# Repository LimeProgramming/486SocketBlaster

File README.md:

# Ignore this for the moment please need to fix it when I have the drive to. Sorry but thanks for looking. 

# 486SocketBlaster

486SocketBlaster is a simple voltage adapter for 486 processors. It allows you
to use a 3-volt 486 CPU on an older 5-volt-only motherboard. For example you
can use a DX4 or an Am5x86 on an old 486 motherboard that would normally only
work with 5-volt CPUs. This basically converts any 3-volt CPU to an "Overdrive".

# How does it work ?

It is really simple: All CPU pins are passed through to the motherboard socket,
except for the Vcc. Those are connected to the output of a mini buck converter
that can be soldered to the 486SocketBlaster board.

# Soldering/Assembly Instructions

This board is not the easiest thing to solder, but can be done with a standard
soldering iron and some patience.
The best way to solder the headers is to start with the innermost one and work
outwards in a spiral manner alternating between the top and bottom side as
needed (see image below). This way you only work on the outside and can easily
reach all the pins.

A desoldering gun may be useful when you accidentally clog up other holes. But
it is probably best to be very careful and avoid clogging them in the first
place. Also using flux makes it easier.

Please make sure you check the solder joints (also check for continuity) before
you add another row of headers on the same side, because the new row will
permanently block your access to the solder joints!
Desoldering a header is almost impossible even with a desoldering gun due to the
very tight hole tolerances.
So it has to be soldered correctly from the first try.

# Voltage regulator

The 486SocketBlaster can be powered by a cheap of-the-shelf buck converter, or
by an external one. The circuit board accepts two common types of small voltage
buck converters, usually found using keywords like "mini buck converter".
These are commonly rated at up to 3A of current. Given that 3-volt 486 CPUs are
usually very efficient (the DX4-100 is rated at max 3.55/5.22W typical/max) such
a regulator should be adequate in most cases.

If you are planning to overclock or to use a more power hungry CPU, please use
an external regulation circuit.

# WARNING!!!

Please make sure you know what you are doing!
Improper assembly/settings/use can damage both your precious motherboard and your precious CPU!

# Bonus Features

- External Power Header. This can be used either for monitoring the CPU voltage,
or for providing power externally, either with an external power supply or an
external voltage regulator.
- CPUMUL Header for selecting/overriding the CPU multiplier. This may be useful
for reducing the multiplier of a DX4 to 2x (66MHz) or Am5x86 to 3x (100MHz).

# Bill of materials

Item                            | ##  | Description
--------------------------------|-----|--------------------------------------------------------
mini buck converter             | 1   | We support two common sizes: 22x17mm and 18x12mm. These usually have chips like MP1584, MP2307 and others
40pin SIP pin header (male)     | 5   | Single-row round pin 2.54mm pitch (male). Socket pin diameter: 0.5mm, PCB pin diameter: 0.6mm. (see photo below)
40pin SIP socket header (female)| 5   | Single-row round pin sockets, 2.54mm pitch. PCB pin diameter: 0.5mm. (see photo below) 
SMD Capacitors                  | 4   | 10uF SMD 1206
Through-hole Capacitor          | 1   | 10uF ceramic through-hole capacitor
3-pin header 2.54mm pitch       | 1   | Header used for selecting the CPU Multiplier (CPUMUL)
Jumper 2.54mm pitch             | 1   | A jumper to for the CPUMUL header

Please note that the headers are a very tight fit. So please make sure that you get headers of the correct pin diameter.

With the limited testing I have done so far, it seems that you need at least
one 10uF through-hole ceramic capacitor, otherwise the voltage ripple is too
high and the system can become unstable with a DX4 @ 100MHz, using a cheap
MP1584-based buck converter.

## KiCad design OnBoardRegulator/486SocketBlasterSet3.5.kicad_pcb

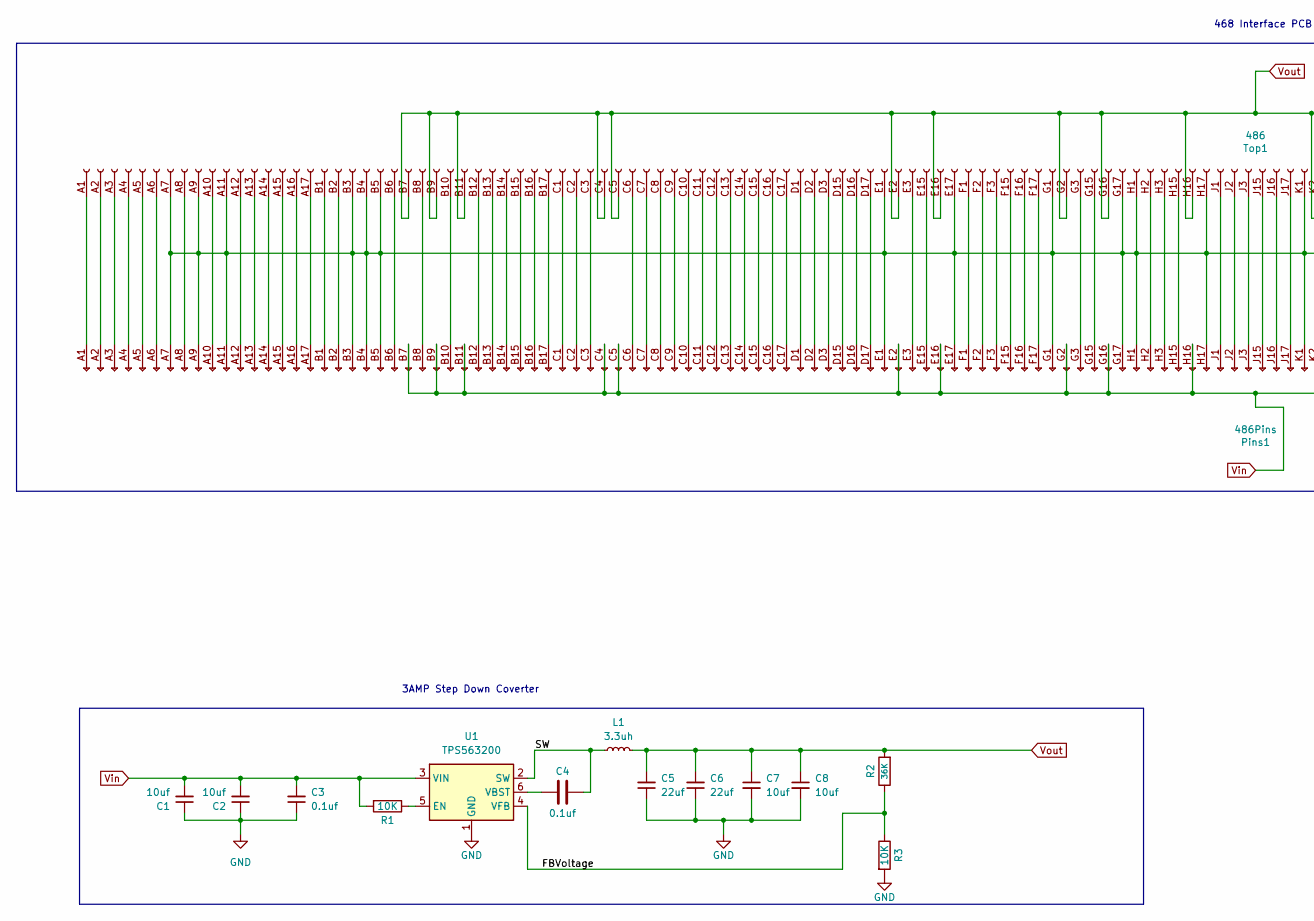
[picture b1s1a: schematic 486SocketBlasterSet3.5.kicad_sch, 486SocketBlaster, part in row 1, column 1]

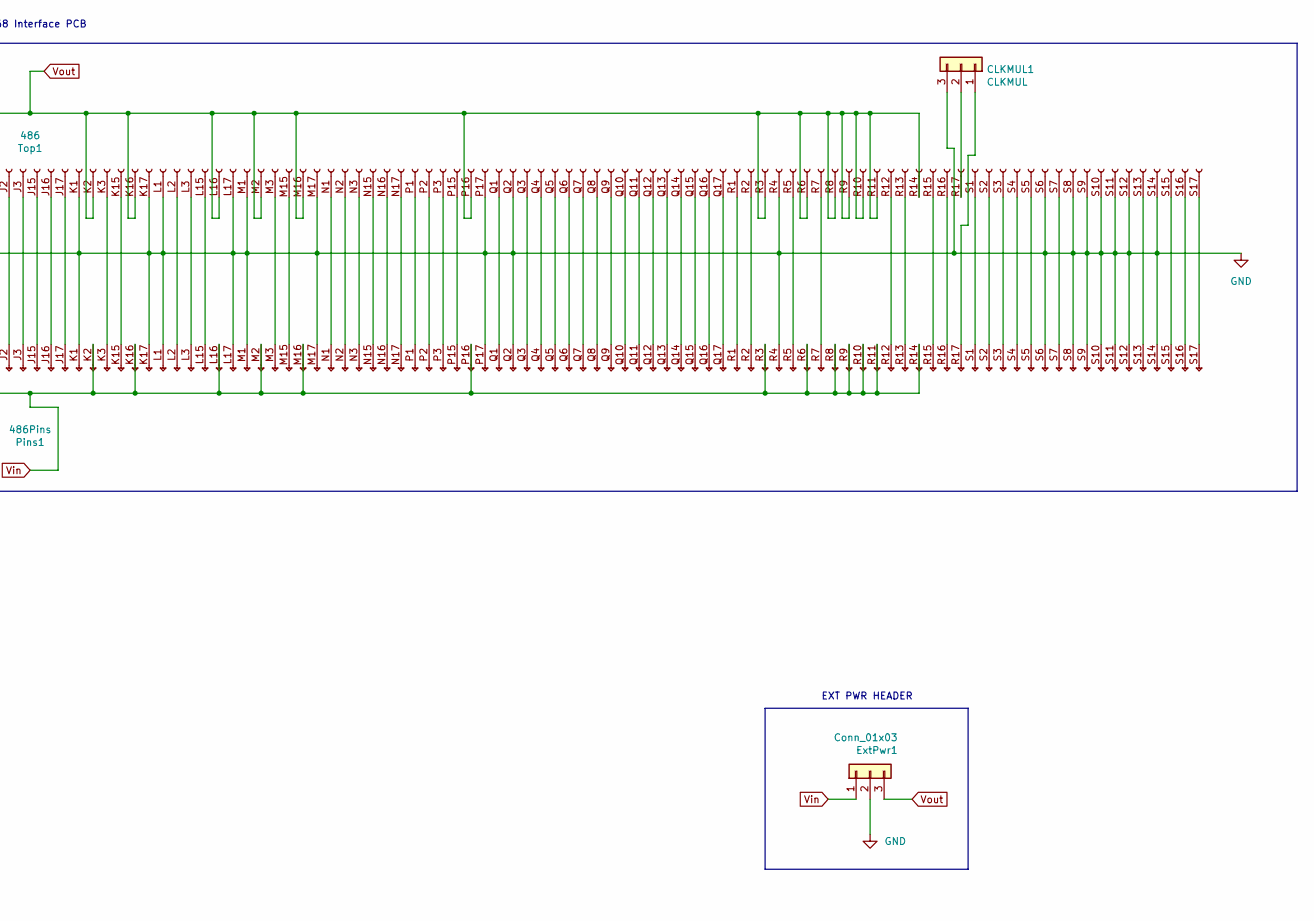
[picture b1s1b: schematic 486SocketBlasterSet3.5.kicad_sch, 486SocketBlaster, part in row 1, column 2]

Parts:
C1, C2, C7, C8: 10uf; C_0805_2012Metric; JLCPCB C15850
C3, C4: 0.1uf; C_0805_2012Metric; JLCPCB C49678
C5, C6: 22uf; C_1206_3216Metric; JLCPCB C12891
CLKMUL1: CLKMUL; PinHeader_1x03_P2.54mm_Vertical
ExtPwr1: Conn_01x03; PinHeader_1x03_P2.54mm_Vertical
L1: 3.3uh; L_5.5x5.5; JLCPCB C436534
Pins1: 486Pins; 486_168pga_pins
R1, R3: 10K; R_0603_1608Metric; JLCPCB C25804
R2: 36K; R_0603_1608Metric; JLCPCB for set C23147
Top1: 486; 486_168pga_socket
U1: TPS563200; SOT-23-6; LCSC C97253

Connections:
/FBVoltage: R2.1, R3.1, U1.4 (VFB)
/SW: C4.2, L1.1, U1.2 (SW)
GND: C1.1, C2.1, C3.1, C5.1, C6.1, C7.2, C8.2, CLKMUL1.3, ExtPwr1.2, Pins1.A7 (Pin_7), Pins1.A9 (Pin_9), Pins1.A11 (Pin_11), Pins1.B3 (Pin_3), Pins1.B4 (Pin_4), Pins1.B5 (Pin_5), Pins1.E1 (Pin_1), Pins1.E17 (Pin_17), Pins1.G1 (Pin_1), Pins1.G17 (Pin_17), Pins1.H1 (Pin_1), Pins1.H17 (Pin_17), Pins1.K1 (Pin_1), Pins1.K17 (Pin_17), Pins1.L1 (Pin_1), Pins1.L17 (Pin_17), Pins1.M1 (Pin_1), Pins1.M17 (Pin_17), Pins1.P17 (Pin_17), Pins1.Q2 (Pin_2), Pins1.R4 (Pin_4), Pins1.S6 (Pin_6), Pins1.S8 (Pin_8), Pins1.S9 (Pin_9), Pins1.S10 (Pin_10), Pins1.S11 (Pin_11), Pins1.S12 (Pin_12), Pins1.S14 (Pin_14), R3.2, Top1.A7 (Pin_7), Top1.A9 (Pin_9), Top1.A11 (Pin_11), Top1.B3 (Pin_3), Top1.B4 (Pin_4), Top1.B5 (Pin_5), Top1.E1 (Pin_1), Top1.E17 (Pin_17), Top1.G1 (Pin_1), Top1.G17 (Pin_17), Top1.H1 (Pin_1), Top1.H17 (Pin_17), Top1.K1 (Pin_1), Top1.K17 (Pin_17), Top1.L1 (Pin_1), Top1.L17 (Pin_17), Top1.M1 (Pin_1), Top1.M17 (Pin_17), Top1.P17 (Pin_17), Top1.Q2 (Pin_2), Top1.R4 (Pin_4), Top1.S6 (Pin_6), Top1.S8 (Pin_8), Top1.S9 (Pin_9), Top1.S10 (Pin_10), Top1.S11 (Pin_11), Top1.S12 (Pin_12), Top1.S14 (Pin_14), U1.1 (GND)
unnamed: C4.1, U1.6 (VBST)
unnamed: CLKMUL1.1, Pins1.R17 (Pin_17)
unnamed: CLKMUL1.2, Top1.R17 (Pin_17)
unnamed: Pins1.A1 (Pin_1), Top1.A1 (Pin_1)
unnamed: Pins1.A2 (Pin_2), Top1.A2 (Pin_2)
unnamed: Pins1.A3 (Pin_3), Top1.A3 (Pin_3)
unnamed: Pins1.A4 (Pin_4), Top1.A4 (Pin_4)
unnamed: Pins1.A5 (Pin_5), Top1.A5 (Pin_5)
unnamed: Pins1.A6 (Pin_6), Top1.A6 (Pin_6)
unnamed: Pins1.A8 (Pin_8), Top1.A8 (Pin_8)
unnamed: Pins1.A10 (Pin_10), Top1.A10 (Pin_10)
unnamed: Pins1.A12 (Pin_12), Top1.A12 (Pin_12)
unnamed: Pins1.A13 (Pin_13), Top1.A13 (Pin_13)
unnamed: Pins1.A14 (Pin_14), Top1.A14 (Pin_14)
unnamed: Pins1.A15 (Pin_15), Top1.A15 (Pin_15)
unnamed: Pins1.A16 (Pin_16), Top1.A16 (Pin_16)
unnamed: Pins1.A17 (Pin_17), Top1.A17 (Pin_17)
unnamed: Pins1.B1 (Pin_1), Top1.B1 (Pin_1)
unnamed: Pins1.B2 (Pin_2), Top1.B2 (Pin_2)
unnamed: Pins1.B6 (Pin_6), Top1.B6 (Pin_6)
unnamed: Pins1.B8 (Pin_8), Top1.B8 (Pin_8)
unnamed: Pins1.B10 (Pin_10), Top1.B10 (Pin_10)
unnamed: Pins1.B12 (Pin_12), Top1.B12 (Pin_12)
unnamed: Pins1.B13 (Pin_13), Top1.B13 (Pin_13)
unnamed: Pins1.B14 (Pin_14), Top1.B14 (Pin_14)
unnamed: Pins1.B15 (Pin_15), Top1.B15 (Pin_15)
unnamed: Pins1.B16 (Pin_16), Top1.B16 (Pin_16)
unnamed: Pins1.B17 (Pin_17), Top1.B17 (Pin_17)
unnamed: Pins1.C1 (Pin_1), Top1.C1 (Pin_1)
unnamed: Pins1.C2 (Pin_2), Top1.C2 (Pin_2)
unnamed: Pins1.C3 (Pin_3), Top1.C3 (Pin_3)
unnamed: Pins1.C6 (Pin_6), Top1.C6 (Pin_6)
unnamed: Pins1.C7 (Pin_7), Top1.C7 (Pin_7)
unnamed: Pins1.C8 (Pin_8), Top1.C8 (Pin_8)
unnamed: Pins1.C9 (Pin_9), Top1.C9 (Pin_9)
unnamed: Pins1.C10 (Pin_10), Top1.C10 (Pin_10)
unnamed: Pins1.C11 (Pin_11), Top1.C11 (Pin_11)
unnamed: Pins1.C12 (Pin_12), Top1.C12 (Pin_12)
unnamed: Pins1.C13 (Pin_13), Top1.C13 (Pin_13)
unnamed: Pins1.C14 (Pin_14), Top1.C14 (Pin_14)
unnamed: Pins1.C15 (Pin_15), Top1.C15 (Pin_15)
unnamed: Pins1.C16 (Pin_16), Top1.C16 (Pin_16)
unnamed: Pins1.C17 (Pin_17), Top1.C17 (Pin_17)
unnamed: Pins1.D1 (Pin_1), Top1.D1 (Pin_1)
unnamed: Pins1.D2 (Pin_2), Top1.D2 (Pin_2)
unnamed: Pins1.D3 (Pin_3), Top1.D3 (Pin_3)
unnamed: Pins1.D15 (Pin_15), Top1.D15 (Pin_15)
unnamed: Pins1.D16 (Pin_16), Top1.D16 (Pin_16)
unnamed: Pins1.D17 (Pin_17), Top1.D17 (Pin_17)
unnamed: Pins1.E3 (Pin_3), Top1.E3 (Pin_3)
unnamed: Pins1.E15 (Pin_15), Top1.E15 (Pin_15)
unnamed: Pins1.F1 (Pin_1), Top1.F1 (Pin_1)
unnamed: Pins1.F2 (Pin_2), Top1.F2 (Pin_2)
unnamed: Pins1.F3 (Pin_3), Top1.F3 (Pin_3)
unnamed: Pins1.F15 (Pin_15), Top1.F15 (Pin_15)
unnamed: Pins1.F16 (Pin_16), Top1.F16 (Pin_16)
unnamed: Pins1.F17 (Pin_17), Top1.F17 (Pin_17)
unnamed: Pins1.G3 (Pin_3), Top1.G3 (Pin_3)
unnamed: Pins1.G15 (Pin_15), Top1.G15 (Pin_15)
unnamed: Pins1.H2 (Pin_2), Top1.H2 (Pin_2)
unnamed: Pins1.H3 (Pin_3), Top1.H3 (Pin_3)
unnamed: Pins1.H15 (Pin_15), Top1.H15 (Pin_15)
unnamed: Pins1.J1 (Pin_1), Top1.J1 (Pin_1)
unnamed: Pins1.J2 (Pin_2), Top1.J2 (Pin_2)
unnamed: Pins1.J3 (Pin_3), Top1.J3 (Pin_3)
unnamed: Pins1.J15 (Pin_15), Top1.J15 (Pin_15)
unnamed: Pins1.J16 (Pin_16), Top1.J16 (Pin_16)
unnamed: Pins1.J17 (Pin_17), Top1.J17 (Pin_17)
unnamed: Pins1.K3 (Pin_3), Top1.K3 (Pin_3)
unnamed: Pins1.K15 (Pin_15), Top1.K15 (Pin_15)
unnamed: Pins1.L2 (Pin_2), Top1.L2 (Pin_2)
unnamed: Pins1.L3 (Pin_3), Top1.L3 (Pin_3)
unnamed: Pins1.L15 (Pin_15), Top1.L15 (Pin_15)
unnamed: Pins1.M3 (Pin_3), Top1.M3 (Pin_3)
unnamed: Pins1.M15 (Pin_15), Top1.M15 (Pin_15)
unnamed: Pins1.N1 (Pin_1), Top1.N1 (Pin_1)
unnamed: Pins1.N2 (Pin_2), Top1.N2 (Pin_2)
unnamed: Pins1.N3 (Pin_3), Top1.N3 (Pin_3)
unnamed: Pins1.N15 (Pin_15), Top1.N15 (Pin_15)
unnamed: Pins1.N16 (Pin_16), Top1.N16 (Pin_16)
unnamed: Pins1.N17 (Pin_17), Top1.N17 (Pin_17)
unnamed: Pins1.P1 (Pin_1), Top1.P1 (Pin_1)
unnamed: Pins1.P2 (Pin_2), Top1.P2 (Pin_2)
unnamed: Pins1.P3 (Pin_3), Top1.P3 (Pin_3)
unnamed: Pins1.P15 (Pin_15), Top1.P15 (Pin_15)
unnamed: Pins1.Q1 (Pin_1), Top1.Q1 (Pin_1)
unnamed: Pins1.Q3 (Pin_3), Top1.Q3 (Pin_3)
unnamed: Pins1.Q4 (Pin_4), Top1.Q4 (Pin_4)
unnamed: Pins1.Q5 (Pin_5), Top1.Q5 (Pin_5)
unnamed: Pins1.Q6 (Pin_6), Top1.Q6 (Pin_6)
unnamed: Pins1.Q7 (Pin_7), Top1.Q7 (Pin_7)
unnamed: Pins1.Q8 (Pin_8), Top1.Q8 (Pin_8)
unnamed: Pins1.Q9 (Pin_9), Top1.Q9 (Pin_9)
unnamed: Pins1.Q10 (Pin_10), Top1.Q10 (Pin_10)
unnamed: Pins1.Q11 (Pin_11), Top1.Q11 (Pin_11)
unnamed: Pins1.Q12 (Pin_12), Top1.Q12 (Pin_12)
unnamed: Pins1.Q13 (Pin_13), Top1.Q13 (Pin_13)
unnamed: Pins1.Q14 (Pin_14), Top1.Q14 (Pin_14)
unnamed: Pins1.Q15 (Pin_15), Top1.Q15 (Pin_15)
unnamed: Pins1.Q16 (Pin_16), Top1.Q16 (Pin_16)
unnamed: Pins1.Q17 (Pin_17), Top1.Q17 (Pin_17)
unnamed: Pins1.R1 (Pin_1), Top1.R1 (Pin_1)
unnamed: Pins1.R2 (Pin_2), Top1.R2 (Pin_2)
unnamed: Pins1.R5 (Pin_5), Top1.R5 (Pin_5)
unnamed: Pins1.R7 (Pin_7), Top1.R7 (Pin_7)
unnamed: Pins1.R12 (Pin_12), Top1.R12 (Pin_12)
unnamed: Pins1.R13 (Pin_13), Top1.R13 (Pin_13)
unnamed: Pins1.R15 (Pin_15), Top1.R15 (Pin_15)
unnamed: Pins1.R16 (Pin_16), Top1.R16 (Pin_16)
unnamed: Pins1.S1 (Pin_1), Top1.S1 (Pin_1)
unnamed: Pins1.S2 (Pin_2), Top1.S2 (Pin_2)
unnamed: Pins1.S3 (Pin_3), Top1.S3 (Pin_3)
unnamed: Pins1.S4 (Pin_4), Top1.S4 (Pin_4)
unnamed: Pins1.S5 (Pin_5), Top1.S5 (Pin_5)
unnamed: Pins1.S7 (Pin_7), Top1.S7 (Pin_7)
unnamed: Pins1.S13 (Pin_13), Top1.S13 (Pin_13)
unnamed: Pins1.S15 (Pin_15), Top1.S15 (Pin_15)
unnamed: Pins1.S16 (Pin_16), Top1.S16 (Pin_16)
unnamed: Pins1.S17 (Pin_17), Top1.S17 (Pin_17)
unnamed: R1.1, U1.5 (EN)
Vin: C1.2, C2.2, C3.2, ExtPwr1.1, Pins1.B7 (Pin_7), Pins1.B9 (Pin_9), Pins1.B11 (Pin_11), Pins1.C4 (Pin_4), Pins1.C5 (Pin_5), Pins1.E2 (Pin_2), Pins1.E16 (Pin_16), Pins1.G2 (Pin_2), Pins1.G16 (Pin_16), Pins1.H16 (Pin_16), Pins1.K2 (Pin_2), Pins1.K16 (Pin_16), Pins1.L16 (Pin_16), Pins1.M2 (Pin_2), Pins1.M16 (Pin_16), Pins1.P16 (Pin_16), Pins1.R3 (Pin_3), Pins1.R6 (Pin_6), Pins1.R8 (Pin_8), Pins1.R9 (Pin_9), Pins1.R10 (Pin_10), Pins1.R11 (Pin_11), Pins1.R14 (Pin_14), R1.2, U1.3 (VIN)
Vout: C5.2, C6.2, C7.1, C8.1, ExtPwr1.3, L1.2, R2.2, Top1.B7 (Pin_7), Top1.B9 (Pin_9), Top1.B11 (Pin_11), Top1.C4 (Pin_4), Top1.C5 (Pin_5), Top1.E2 (Pin_2), Top1.E16 (Pin_16), Top1.G2 (Pin_2), Top1.G16 (Pin_16), Top1.H16 (Pin_16), Top1.K2 (Pin_2), Top1.K16 (Pin_16), Top1.L16 (Pin_16), Top1.M2 (Pin_2), Top1.M16 (Pin_16), Top1.P16 (Pin_16), Top1.R3 (Pin_3), Top1.R6 (Pin_6), Top1.R8 (Pin_8), Top1.R9 (Pin_9), Top1.R10 (Pin_10), Top1.R11 (Pin_11), Top1.R14 (Pin_14)

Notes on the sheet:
468 Interface PCB
EXT PWR HEADER
3AMP Step Down Coverter

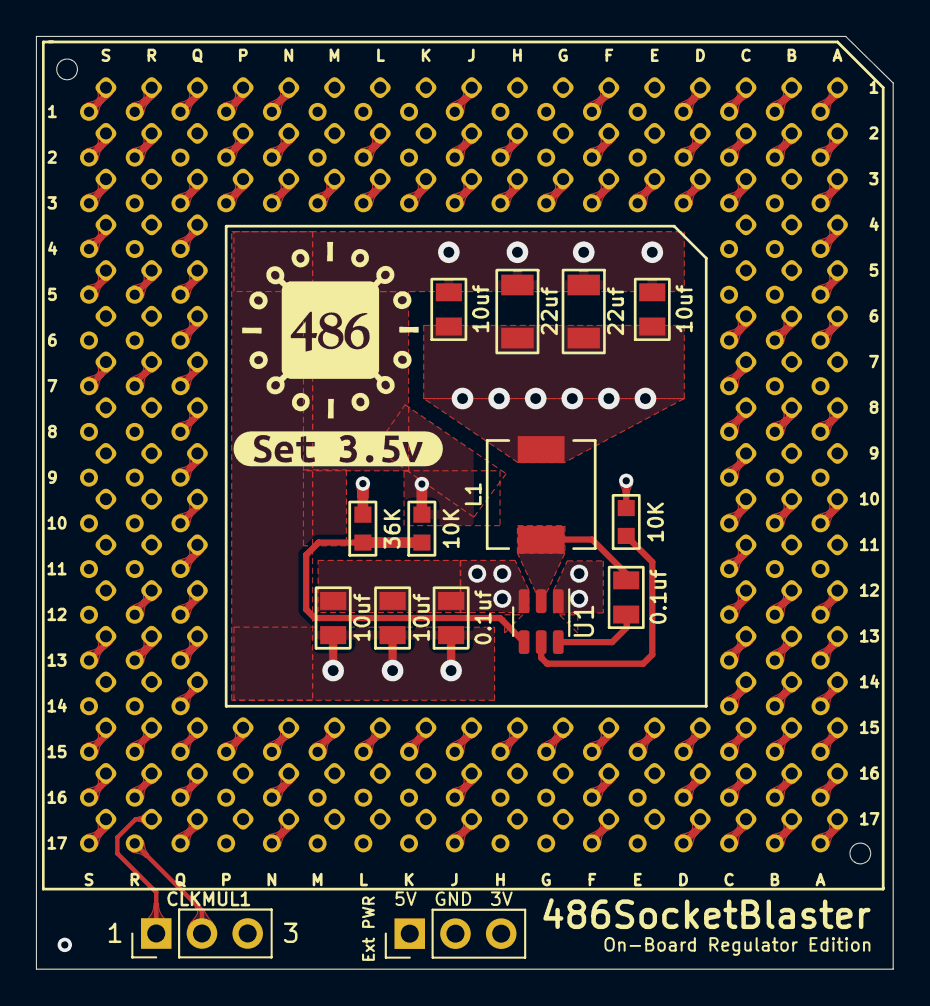
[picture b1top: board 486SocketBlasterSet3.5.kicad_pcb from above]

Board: 4 copper layers, 47.6 x 51.8 mm, 18 parts (0 on the bottom side), 125 nets.

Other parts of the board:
kibuzzard-64864674: G***; kibuzzard-64864674

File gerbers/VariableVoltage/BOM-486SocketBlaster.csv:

Comment,Designator,Footprint,JLCPCB
40.2K,R4,R_0603_1608Metric,C12447
22uf,"C5,C6,C7,C8",C_1206_3216Metric,C12891
10uf,"C1,C2",C_0805_2012Metric,C15850
10K,"R1,R3",R_0603_1608Metric,C25804
68.1K,R2,R_0603_1608Metric,C23231
0.1uf,"C3,C4",C_0805_2012Metric,C28233
3.3uh,L1,L_5.5x5.5,C436534
TPS563200,U1,SOT-23-6,C97253
100K,RV1,tinySMDpot,C719186

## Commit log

2023-06-12 remove original kicad files
2023-06-12 add folder
2023-06-12 Initial Upload
2023-06-12 initial upload of gerbers
2023-06-12 add readme
2023-06-12 add bom and cpl
2023-06-12 add image fix gerbers
